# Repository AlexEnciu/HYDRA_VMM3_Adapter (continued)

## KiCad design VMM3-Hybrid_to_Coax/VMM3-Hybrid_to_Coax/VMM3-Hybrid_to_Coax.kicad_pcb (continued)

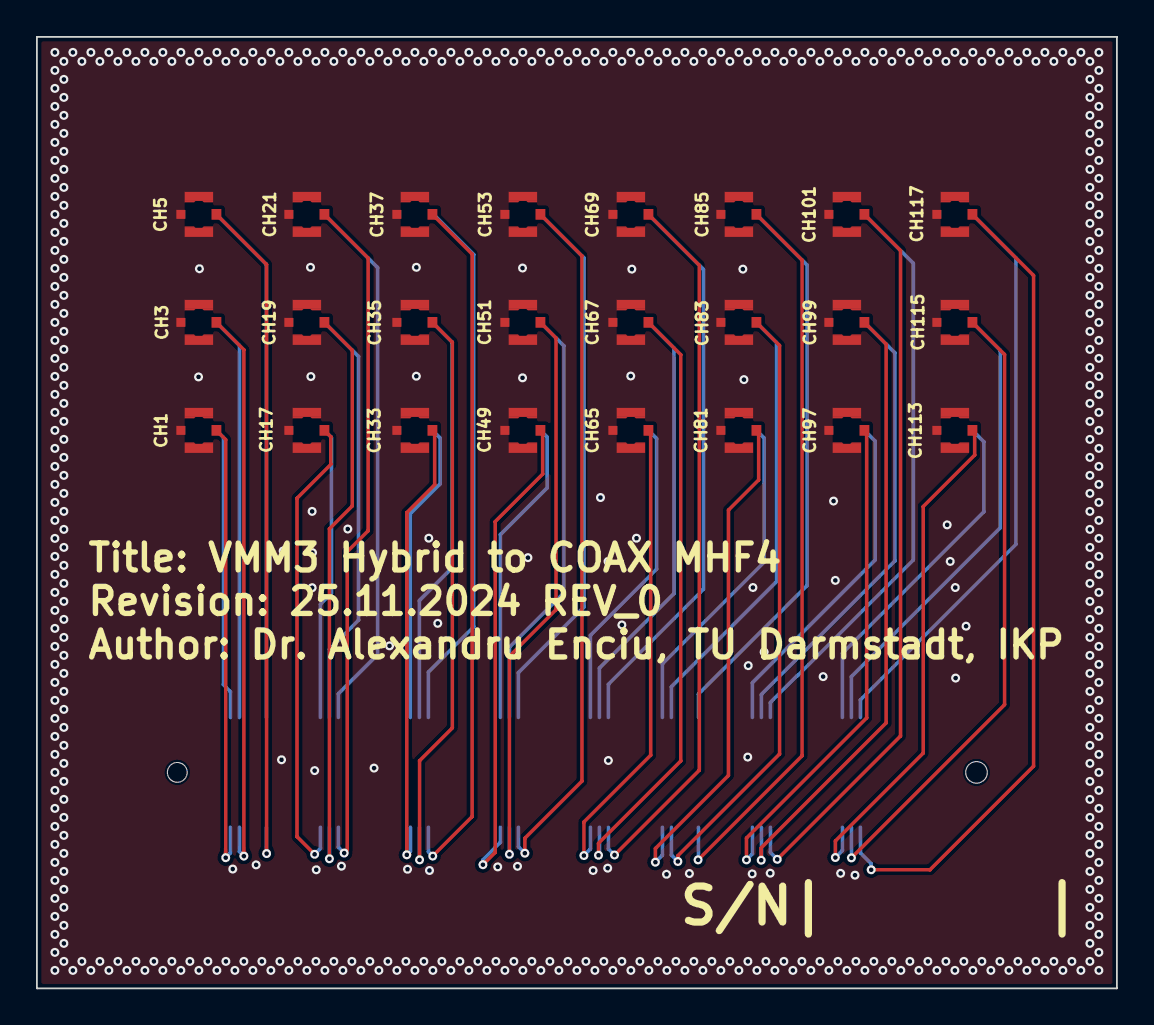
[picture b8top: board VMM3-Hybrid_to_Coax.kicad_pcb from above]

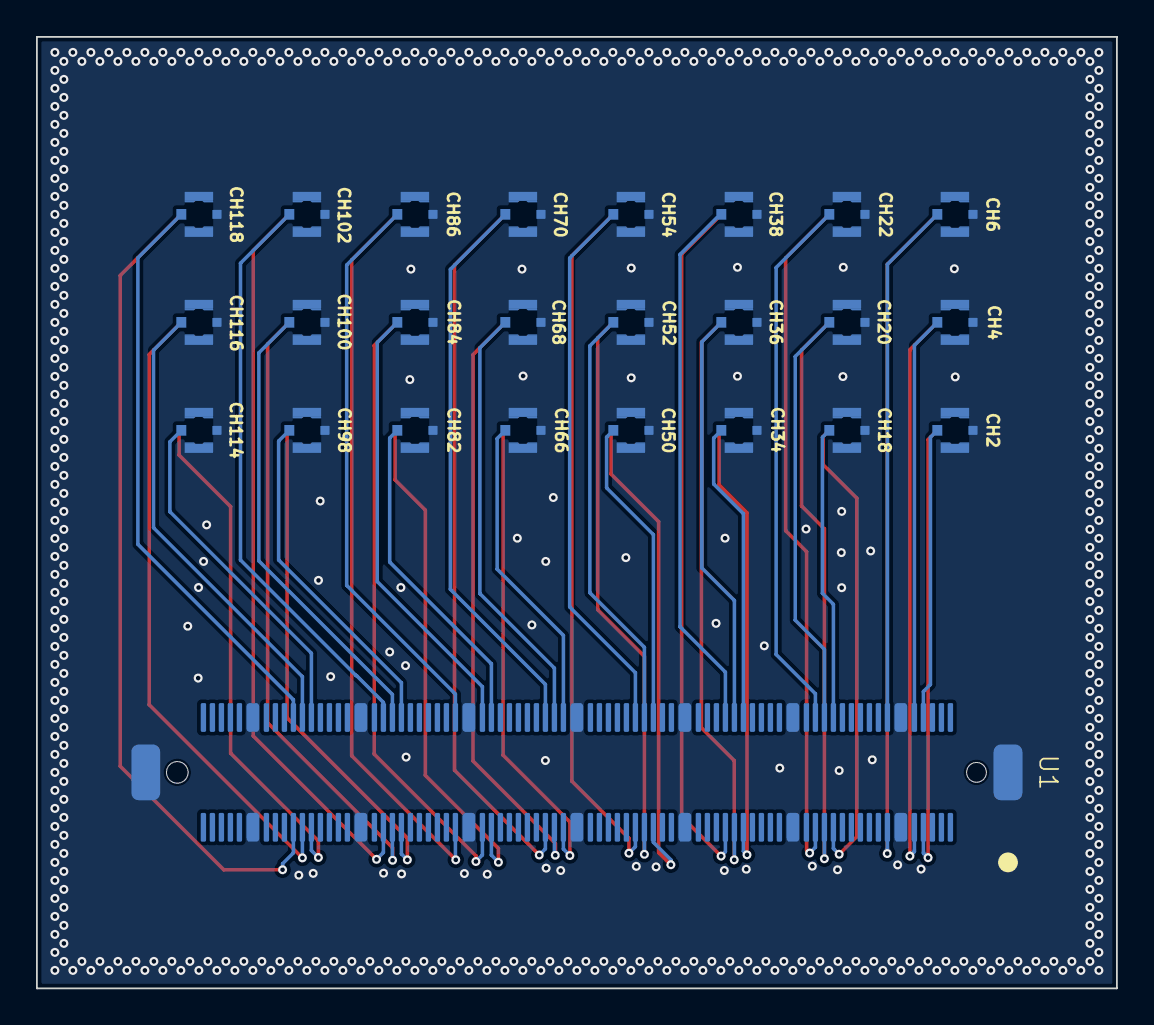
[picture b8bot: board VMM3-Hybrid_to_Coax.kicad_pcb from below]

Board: 4 copper layers, 60.0 x 52.9 mm, 49 parts (25 on the bottom side), 49 nets.
